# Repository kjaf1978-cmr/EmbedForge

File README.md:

# NETApps Electric Simulation

(Formerly EmbedForge; renamed by decision D18. The repository keeps its name.)

An offline-first desktop application that turns a plain-English description and a target
board into a verified, documented Arduino / Raspberry Pi / Pico project: firmware, pin map,
schematic, breadboard, PCB or perfboard, manufacturing files, BOM, emulation and assembly
guide.

Licence: GPL-3.0-or-later (LICENSE file added with the first code, Increment 1).

## Current state
**Version 0.2.0: Increment 2, schematic entry and circuit simulation** (decision D17, prompt
v3.9: design tools first).
- Schematic editor with a generic part library and live electrical rule check.
- Circuit simulator: operating point, transient, AC and DC sweep, cross-checked against
  ngspice; probes and a waveform viewer.
- Start screen with examples and a tutorial; projects with version history; SVG, PNG, SPICE
  and CSV export.

Next: Increment 3, PCB layout and routing. Increment 1 (shell, signed offline installers,
integrity check) is delivered as 0.1.0.

- Requirements baseline: `docs/requirements/EmbedForge_prompt_v3.9.md`
- Current increment: `docs/inc2/` (scope, test report, usability)
- Decisions: `docs/phase0/STATUS.md`; session log: `docs/SESSION_LOG.md`

## Layout
```
docs/requirements/   build prompt baselines, review findings, change logs
docs/phase0/         Phase 0 deliverables (a)–(o)
docs/inc1/           Increment 1 scope, reports, findings, user-executed procedures
docs/inc2/           Increment 2 scope, test report, usability
core/                Rust workspace: ef-schema, ef-cm, ef-integrity, ef-host, ef-diag,
                     ef-pack, ef-release, ef-install (embedforge-setup), ef-helper
packaging/           installation media: staging, signing scripts, .deb, specs, CI tests
app/ui/              UI (Preact + TypeScript + Vite), unit and browser tests
app/src-tauri/       Tauri 2 desktop shell
spikes/              Phase 0 evaluation code (not application code)
.github/workflows/   CI
tools/               scripts used to produce or check documents
```

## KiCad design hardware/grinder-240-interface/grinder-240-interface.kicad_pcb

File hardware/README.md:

# Boards of the worked designs (decisions D43, D44)

Each design's board as a KiCad 7 project, with its fabrication files. The boards are generated
from the app's schematics by `tools/kicad` and then checked with KiCad's design rule check
(DRC); do not edit the board files by hand without updating the plan in
`tools/kicad/layouts.ts`, or the next export overwrites the change.

| Design | Folder | Board | DRC (errors / unconnected) | Status |
|---|---|---|---|---|
| Mains voltage stabiliser 1 kVA (P4) | `stabiliser/` | 230 × 212 mm, 2 layers, 2 oz | 0 / 0 | routed; awaiting a person's review and a prototype |
| Mains change-over 1P, 32 A (P3): control board + DIN-rail panel | `changeover-1p/` | 155 × 110 mm, 2 layers, 2 oz | 0 / 0 | routed; panel wiring in `panel.csv` |
| Mains change-over 3P+N, 32 A (P3): control board + DIN-rail panel | `changeover-3p/` | 225 × 150 mm, 2 layers, 2 oz | 0 / 0 | routed; panel wiring in `panel.csv` |
| MPPT solar charger 48 V, 80 A (P6): power board | `mppt-power/` | 280 × 160 mm, 2 layers, 4 oz | 0 / 0 | routed; copper bars and lugs below |
| MPPT solar charger 48 V, 80 A (P6): control board | `mppt-control/` | 160 × 110 mm, 2 layers, 2 oz | 0 / 0 | routed; `link.csv`: the nets to the power board |
| Inverter 48 V 5 kW, 50 Hz transformer (P7a): power board | `inverter-lf-48-power/` | 280 × 170 mm, 2 layers, 4 oz | 0 / 0 | routed; copper bars and lugs, bus and ground planes |
| Inverter 48 V 5 kW, 50 Hz transformer (P7a): control board | `inverter-lf-48-control/` | 200 × 150 mm, 2 layers, 2 oz | 0 / 0 | routed; mains nets 3.2 mm apart |
| Inverter 48 V 5 kW, high-frequency (P7b): battery-side power board | `inverter-hf-48-power-lv/` | 180 × 230 mm, 2 layers, 4 oz | 0 / 0 | routed; copper bars, the current transformer off-board |
| Inverter 48 V 5 kW, high-frequency (P7b): 380 V power board | `inverter-hf-48-power-hv/` | 140 × 270 mm, 2 layers, 4 oz | 0 / 0 | routed; conformal coating required (0.8 mm, IPC-2221 B4); the drivers' HVG poured after routing |
| Inverter 48 V 5 kW, high-frequency (P7b): battery-side control board | `inverter-hf-48-control-lv/` | 220 × 160 mm, 2 layers, 2 oz | 0 / 0 | routed; `panel.csv`: the nets to the other boards (J_PANEL, J_PANEL2) |
| Inverter 48 V 5 kW, high-frequency (P7b): 380 V control board | `inverter-hf-48-control-hv/` | 340 × 240 mm, 2 layers, 2 oz | 0 / 0 | routed; 380 V nets 2.5 mm from the battery side; HVG poured on both layers; 77 links drawn by `tools/kicad/autolink.py`; `panel.csv`: the nets to the other boards |
| Inverter 12 V 1.5 kW, 50 Hz transformer (P7a): power board | `inverter-lf-12-power/` | 280 × 170 mm, 2 layers, 4 oz | 0 / 0 | routed; the 48 V board's plan with six 4700 µF bus capacitors |
| Inverter 12 V 1.5 kW, 50 Hz transformer (P7a): control board | `inverter-lf-12-control/` | 200 × 150 mm, 2 layers, 2 oz | 0 / 0 | routed; mains nets 3.2 mm apart; one link drawn by `tools/kicad/link.py` |
| Inverter 12 V 1.5 kW, high-frequency (P7b): battery-side power board | `inverter-hf-12-power-lv/` | 260 × 230 mm, 2 layers, 4 oz | 0 / 0 | routed; three MOSFETs per switch (twelve in the row), copper bars |
| Inverter 12 V 1.5 kW, high-frequency (P7b): 380 V power board | `inverter-hf-12-power-hv/` | 140 × 270 mm, 2 layers, 4 oz | 0 / 0 | routed; the 48 V board's plan; conformal coating required |
| Inverter 12 V 1.5 kW, high-frequency (P7b): battery-side control board | `inverter-hf-12-control-lv/` | 220 × 160 mm, 2 layers, 2 oz | 0 / 0 | routed; `panel.csv`: the nets to the other boards |
| Inverter 12 V 1.5 kW, high-frequency (P7b): 380 V control board | `inverter-hf-12-control-hv/` | 340 × 240 mm, 2 layers, 2 oz | 0 / 0 | routed; as the 48 V one (HVG pours, links by `autolink.py`) |
| Gate controller 24 V (P9, D25): motor drive, protections, Arduino Nano and IR receiver | `gate-controller/` | 160 × 110 mm, 2 layers, 2 oz | 0 / 0 | routed; the Nano on sockets, the TSOP38238 behind the enclosure's window; one supply link drawn by `tools/kicad/link.py` |
| Pump controller (P9): control board + DIN-rail panel | `pump-control/` | 165 × 110 mm, 2 layers, 2 oz | 0 / 0 | routed; mains nets 3.2 mm apart; panel wiring in `panel.csv` |
| Cordless trimmer drive 36 V (P9) | `trimmer-drive/` | 160 × 100 mm, 2 layers, 4 oz | 0 / 0 | routed; power on 3 mm tracks, ground poured on both layers |
| Block moulding machine (P9): safety circuit, 24 V outputs, inputs and Arduino Nano + DIN-rail panel | `block-machine/` | 170 × 120 mm, 2 layers, 2 oz | 0 / 0 | routed; the pump, mixer and vibrator contactors, E-stop and safety contactors on the DIN rail, wiring in `panel.csv`; no 400 V net on the board |
| Irrigation controller (P9, D24): main board | `irrigation-main/` | 130 × 100 mm, 2 layers, 2 oz | 0 / 0 | routed; ESP32-DevKitC on sockets (antenna over the top edge), 24 V in, bus to the modules (20-way ribbon) |
| Irrigation controller (P9, D24): 8-zone channel module (1 … 8 per controller) | `irrigation-module/` | 230 × 95 mm, 2 layers, 2 oz | 0 / 0 | routed; field terminals along the bottom edge (per zone: valve +24 V, valve out, sensor +3.3 V, signal, 0 V); bus in top left, out top right |
| Grinder drive 2.5 kW, 240 V (P9, D26/D46): power board | `grinder-240-power/` | 160 × 110 mm, 2 layers, 4 oz | 0 / 0 | routed; GBPC3510 bridge and both IKW50N60T on the bottom edge (one heatsink, insulating pads), 3 mm power tracks, ground poured on both layers; the whole board at mains potential: 0.8 mm between nets (1.5 mm around the mains input), conformal coating required; the 15 mH choke, the motor and the contactor KM on the panel (`panel.csv`) |
| Grinder drive 2.5 kW, 240 V (P9, D26/D46): control board | `grinder-240-control/` | 180 × 130 mm, 2 layers, 2 oz | 0 / 0 | routed (the run chain and the speed pot moved to the operator interface board); the five trimmers (MAX, MIN, ACCEL, CURRENT LIMIT, IR COMP), terminals for E-STOP, STOP, START, the thermal switch, the reversing switch's contact and the speed pot; not isolated from the mains (DFMEA GR-9): inside the closed enclosure only; one link drawn by `tools/kicad/link.py` |
| Grinder drive 2.5 kW, 240 V (P9, D26/D46): operator interface board | `grinder-240-interface/` | 120 × 90 mm, 2 layers, 2 oz | 0 / 0 | routed; the PELV side (run chain, E-STOP, STOP, START, thermal and reversing contacts, QEN for the K1 and KM coils, the speed pot with MAX and MIN, its TL431 reference) and the barrier: the AMC1311B (set point) and the PC817 (fault); 5.5 mm between the PELV nets and the control's side (GND, V12, VD2, SPP, SPN, OKA: J_MAINS, its spare pole on V12); TR1 on the panel |
| Grinder drive 2.5 kW, 24 V battery (P9, D26/D46): power board | `grinder-24-power/` | 200 × 130 mm, 2 layers, 4 oz | 0 / 0 | routed; six IRFP4468 on the bottom edge, the switch node a 6 mm bar between the row and the edge (tin it), bus plane over 8 × 2200 µF, ground plane, the motor's return poured to the 0.5 mΩ shunt; M5 lugs for battery +/−, motor A+/A−; the 200 A fuse, KM (250 A) and K1 on the panel |
| Grinder drive 2.5 kW, 24 V battery (P9, D26/D46): control board | `grinder-24-control/` | 180 × 130 mm, 2 layers, 2 oz | 0 / 0 | routed; the 240 V control's circuit with the 24 V scaling and the battery's 21 V cut-off |
| Mains stabiliser 5/10/15 kVA, thyristor taps (P4b, D41): logic board | `stabiliser-t-logic/` | 205 × 140 mm, 2 layers, 2 oz | 0 / 0 | routed; mains nets 3.2 mm apart; thyristors, autotransformer and the pair boards wired per `panel.csv` |
| Mains stabiliser 5/10/15 kVA, thyristor taps (P4b): thyristor pair driver (7 per unit) | `stabiliser-t-pair/` | 120 × 80 mm, 2 layers, 2 oz | 0 / 0 | routed; optotriac isolation to the logic side (DIP-6 with pin 5 removed); `panel.csv`: J_MAINS/J_PANEL wiring |

### The 24 V inverters (P7, 3 kW)

The 24 V units use the 48 V boards: the same parts on each board with the same footprints and
connections, only values differ (`tools/kicad/variant.ts` checks this). The 48 V board's folder
holds the 24 V parts list as `<board>-bom-24v.csv`; order the board's fabrication files as they
are and fit the parts from that list.

## What a folder holds

- `<design>.kicad_pcb`, `.kicad_pro`, `.kicad_dru`: the board, its net classes and the custom
  insulation rule. Open the `.kicad_pro` in KiCad 7 or later.
- `<design>-fabrication.zip`: Gerber (copper, solder mask, silkscreen, outline), Excellon drill
  file and drill map, pick-and-place positions. Upload it to the fab as it is.
- `<design>-copper.pdf` / `.png`: both copper layers, the silkscreen and the outline.
- `<design>-drc.rpt`: KiCad's DRC report of the routed board.
- `panel.csv`: for designs with parts on a panel (DIN rail, chassis), the wiring list.
- `fp-lib-table` with `../NETApps.pretty`: the app's footprints as a KiCad library.

## Rules every board follows

- Mains nets (found from the schematic: everything galvanically joined to L and N, up to the
  transformers, optocouplers and relay coils) are 3.2 mm from every other net, the creepage of
  basic insulation at 300 V r.m.s. (IEC 62368-1, pollution degree 2, material group IIIb); the
  control side is earthed (PE), so basic insulation suffices. Between two mains nets 1.5 mm.
- Mains terminals at 7.62 mm pitch; off-board transformers on connectors with an empty pole
  between their windings.
- Footprints follow each part's value and rating, as the parts list orders it: electrolytics by
  C·V (Ø 5 … 18 mm radial, 22 … 35 mm snap-in), film capacitors by C·V (7.5 … 37.5 mm pitch),
  Y and high-voltage ceramics at 10 mm, resistors by power (¼ W, 1 W, 2–3 W, 5 W and 10 W
  cement, four-terminal shunts), fuses (TR5 to 6.3 A, 5 × 20 mm holder to 10 A), inductors (radial
  to 2 A, toroid to 10 A). Parts above that (power resistors over 10 W, inductors over 10 A, fuses
  over 10 A) sit off the board, on the chassis or heatsink, wired or bolted.
- High-current nets end on M5 bolt lugs (busbars or cable lugs), not on screw terminals.
- Track widths by IPC-2221 for the current at 20 K rise in 2 oz copper (the stabiliser's mains
  tracks 1.6 mm for 7 A).
- The power section is placed and partly routed by a written plan (`tools/kicad/layouts.ts`);
  the control section is placed from the schematic and routed by Freerouting.

## Power boards (D45)

The high-current paths are drawn as 4 mm tracks with the solder mask open on them: solder a
tinned copper bar 4 × 3 mm (12 mm², 80 A at about 30 K rise) along each, or two 4 mm² solid
copper wires, so the bar carries the current and the board's 4 oz copper only joins it to the
pins. Cables and busbars bolt to the M5 lugs (plated holes with 12 mm rings): the inductor and
the fuse sit on the chassis next to the board. The TO-247 and TO-126 parts stand in one row along
the bottom edge, their tabs to a common heatsink (isolate each tab with a thermal pad rated for
the voltage, the PV side reaches 114 V). The two boards of a design connect through their 12-pole
connectors, pole by pole as `link.csv` lists them.

## Parts lists

Each folder's `<design>-bom.csv` lists the parts with the footprint each has on the board, the
manufacturer's part number, distributors with order numbers, and an indicative unit price (EUR,
October 2026, "live" or "estimate"; check prices and stock when ordering). The lines not on
this board come last (panel parts, the other board's parts).

## Known warnings

- `lib_footprint_mismatch` on parts turned 180°: KiCad compares the turned reference text's angle
  with the library copy; the copper is the same.
- `silk_overlap`: reference designators touching outlines (cosmetic; fix by hand before ordering
  if the silkscreen matters).

## Before ordering

These boards come out of the verified schematics, but no one has built them yet. Before a
production order: a person's review of the layout (clearances on the mains side, the heat of the
relays and regulators), and a prototype tested against the design's test plan (TEST_REPORT.md).
Prices and parts: the design document's BOM (`docs` export in the app).

Regenerate a board:

```
cd app/ui && npx vite-node ../../tools/kicad/export.ts stabiliser /tmp/stab
cd ../.. && python3 tools/kicad/route.py /tmp/stab --passes 40
```

Needs KiCad 7 (pcbnew Python module and kicad-cli), Freerouting 1.9 at
/opt/freerouting/freerouting.jar (or `FREEROUTING=`), Java 17+ and xvfb-run.

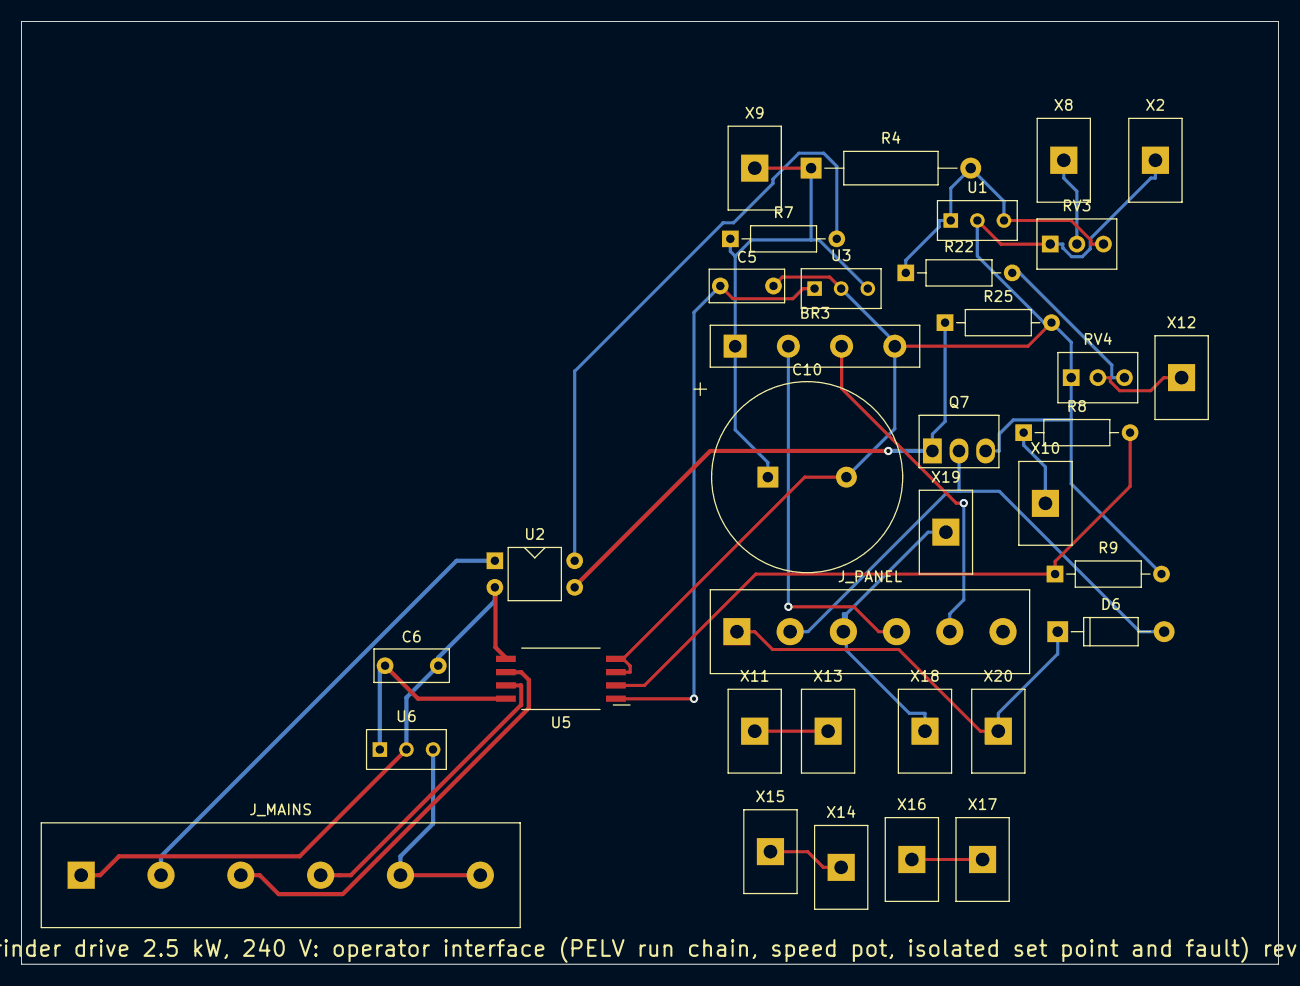
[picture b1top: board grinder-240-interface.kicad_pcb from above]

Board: 2 copper layers, 120.0 x 90.0 mm, 35 parts (0 on the bottom side), 25 nets.

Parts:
BR3: KBP206; Bridge_Inline_4
C5, C6: 100n; C_Disc_5.08
C10: 1000u; CP_Radial_D18
D6: 1N4007; D_DO-41
J_MAINS: mains to the panel; TerminalBlock_1x6_P7.62
J_PANEL: to the panel; TerminalBlock_1x6
Q7: IRLZ44N; TO-220_Vertical
R4: 1.5k; R_Axial_0309
R7, R25: 10k; R_Axial_0207
R8, R9: 100k; R_Axial_0207
R22: 3.9k; R_Axial_0207
RV3, RV4: 1k; Pot_Trimmer_3
U1: TL431; TO-92_Wide
U2: PC817; DIP-4
U3, U6: L78L05; TO-92_Wide
U5: AMC1311B; SOIC-8W
X2: PE: the PELV 0 V bonded to protective earth; TerminalBlock_1x1
X8: speed pot top; TerminalBlock_1x1
X9: E-STOP (NC) from +24 V; TerminalBlock_1x1
X10: speed pot wiper; TerminalBlock_1x1
X11: E-STOP (NC) return; TerminalBlock_1x1
X12: speed pot bottom; TerminalBlock_1x1
X13: STOP (NC); TerminalBlock_1x1
X14: STOP (NC) return; TerminalBlock_1x1
X15: motor thermal switch (NC); TerminalBlock_1x1
X16: motor thermal switch return; TerminalBlock_1x1
X17: reversing switch auxiliary (closed in FWD and REV); TerminalBlock_1x1
X18: reversing switch auxiliary return; TerminalBlock_1x1
X19: START (NO); TerminalBlock_1x1
X20: START (NO) return; TerminalBlock_1x1

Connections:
CH2: D6.1, J_PANEL.1, X20.1
CR: D6.2, J_PANEL.2, Q7.2
ESO: X11.1, X13.1
GND: C6.2, J_MAINS.1, U2.2, U5.5, U6.2
OKA: J_MAINS.2, U2.1
OKC: R7.2, U2.4
OKG: Q7.1, R25.1, U2.3
PE0: BR3.4, C5.2, C10.2, Q7.3, R9.2, R25.2, RV3.1, RV4.1, U1.2, U3.2, U5.3, U5.4, X2.1
RV: J_PANEL.3, X18.1, X19.1
SMN: RV4.2, X12.1
SMX: RV3.2, X8.1
SPN: J_MAINS.3, U5.6
SPP: J_MAINS.4, U5.7
SREF: R4.2, R22.1, RV3.3, U1.1, U1.3
STO: X14.1, X15.1
TA: BR3.2, J_PANEL.4
TB: BR3.3, J_PANEL.5
THO: X16.1, X17.1
V12: J_MAINS.5, J_MAINS.6, U6.3
V24: BR3.1, C10.1, R4.1, R7.1, U3.3, X9.1
VD1: C5.1, U3.1, U5.1
VD2: C6.1, U5.8, U6.1
VMN: R22.2, RV4.3
WIP: R8.1, X10.1
WIPD: R8.2, R9.1, U5.2

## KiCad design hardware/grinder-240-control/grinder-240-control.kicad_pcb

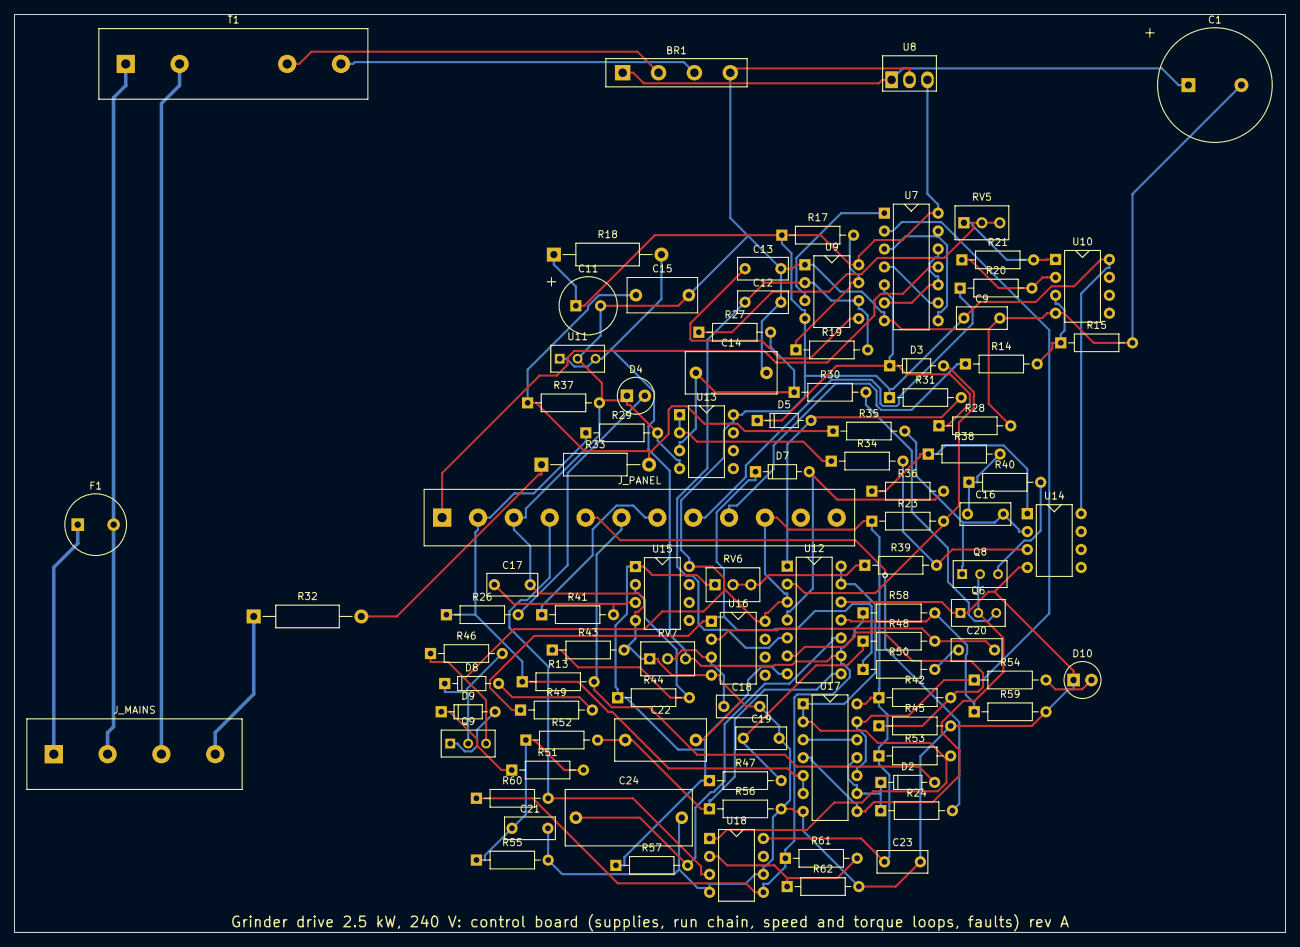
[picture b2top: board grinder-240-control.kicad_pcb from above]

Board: 2 copper layers, 180.0 x 130.0 mm, 94 parts (0 on the bottom side), 69 nets.

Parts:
BR1: KBP206; Bridge_Inline_4
C1: 470u; CP_Radial_D16
C9, C18, C20, C21, C23: 100n; C_Disc_5.08
C11: 47u; CP_Radial_D8
C12, C13: 10n; C_Disc_5.08
C14: 4.7u; C_Film_P10
C15: 2.2u; C_Film_P7.5
C16: 47n; C_Disc_5.08
C17: 1n; C_Disc_5.08
C19: 1u; C_Disc_5.08
C22: 10u; C_Film_P10
C24: 22u; C_Film_P15
D2, D3, D5, D7, D9: 1N4148; D_DO-35
D4: green; LED_D5.0
D8: BZX55C5V1; D_DO-35
D10: red; LED_D5.0
F1: 0.2; F_TR5
J_MAINS: mains to the panel; TerminalBlock_1x4_P7.62
J_PANEL: to the panel; TerminalBlock_1x12
Q6, Q8: 2N7000; TO-92_Wide
Q9: BC557B; TO-92_Wide
R13, R14, R20, R23, R29, R31, R34, R37, R45, R47, R48, R49, R53, R59, R60: 10k; R_Axial_0207
R15, R21: 20k; R_Axial_0207
R17: 6.8k; R_Axial_0207
R18: 470; R_Axial_0309
R19: 330; R_Axial_0207
R24: 4.7k; R_Axial_0207
R26, R36, R54: 2.2k; R_Axial_0207
R27: 22k; R_Axial_0207
R28, R35, R39: 100k; R_Axial_0207
R30, R40: 100; R_Axial_0207
R32, R33: 453k; R_Axial_0309
R38, R55, R56, R57: 1M; R_Axial_0207
R41, R43, R51, R62: 1k; R_Axial_0207
R42: 30.1k; R_Axial_0207
R44: 9.09k; R_Axial_0207
R46, R50: 47k; R_Axial_0207
R52: 330k; R_Axial_0207
R58: 4.42k; R_Axial_0207
R61: 9.31k; R_Axial_0207
RV5, RV6: 1M; Pot_Trimmer_3
RV7: 1k; Pot_Trimmer_3
T1: 0.0625; Transformer_Wires_P7.62
U7, U17: V12; DIP-14
U8: 7812; TO-220_Vertical
U9: NE555; DIP-8
U10, U13, U14, U15, U16: LM358; DIP-8
U11: TL431; TO-92_Wide
U12: LM339; DIP-14
U18: LM393; DIP-8

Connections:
ACW: R27.1, RV5.2, RV5.3
CLE: D9.2, Q9.1
CLF: C21.1, R51.2, R52.1, R55.1
CLJ: D9.1, R51.1
CLK: U7.1, U9.3
CT: C12.1, R19.2, U9.2, U9.6, U12.5
CV: C13.1, U9.5
DIS: R17.2, R19.1, U9.7
DRV: J_PANEL.1, U7.11
DUT: D7.2, R36.2, U12.4
DUTP: R36.1, R38.1, U14.1
EN: J_PANEL.2, R13.1, R26.1, R29.1, U17.5, U17.6
ENL: D4.2, R26.2
ENN: Q6.2, Q8.2, U17.4, U17.8
FBA: R32.2, R33.1
FBD: C15.1, R33.2, R35.1, R37.1
FLT: R54.1, U7.2, U17.10, U17.13
FLTH: U17.3, U17.12
FLTN: R53.2, U12.13, U12.14, U17.1, U17.2, U18.1
GND: BR1.4, C1.2, C9.2, C11.2, C12.2, C13.2, C14.2, C15.2, C17.2, C18.2, C19.2, C21.2, C22.2, C23.2, C24.2, D4.1, D10.1, J_PANEL.3, Q6.1, R15.2, R28.2, R29.2, R37.2, R43.2, R45.2, R55.2, R56.2, R59.2, R62.2, RV7.1, U7.7, U8.2, U9.1, U10.4, U11.2, U12.12, U13.4, U14.4, U15.4, U16.4, U17.7, U18.4, U18.6
IAF: C19.1, R47.2, R48.1
IAV: C22.1, R52.2, R56.1, U12.8
IOL: C24.1, R57.2, U12.10
IRW: R39.1, RV6.2, RV6.3
ISA: R44.1, R47.1, R57.1, RV6.1, U12.7, U15.1
ISN: R43.1, R44.2, U15.2
ISP: C17.1, R41.2, U15.3
JB: D8.1, Q9.2, R46.2
JD1: D8.2, R49.2
L: F1.1, J_MAINS.1
LFA: D10.2, R54.2
LT: F1.2, J_MAINS.2, T1.1
N: J_MAINS.3, T1.2
NTH: J_PANEL.4, R60.2, U18.3
OK: D2.1, R24.1, U17.9, U17.11
OKA: J_PANEL.5, R24.2
PIN: C16.2, Q8.1, R35.2, U14.2
PIQ: Q8.3, R40.2
PIX: C16.1, R38.2, R40.1
Q: U7.4, U7.9
QN: U7.6, U7.10, U7.12
RCLO: D5.2, R31.2, U12.1
RPW: D3.2, R23.2, U12.2
RST: D3.1, D5.1, R28.1, U7.5
SDM: R20.2, R21.1, U10.2
SDN: D2.2, J_PANEL.6, R13.2
SDP: R14.2, R15.1, U10.3
SET: U7.3, U7.8, U7.13
SHN: J_PANEL.7, R41.1
SPB: R34.1, U13.1, U13.2
SPC: R34.2, R39.2, U14.3
SPN: J_PANEL.8, R20.1
SPP: J_PANEL.9, R14.1
SPQ: Q6.3, R30.2
SPR: C14.1, R27.2, R30.1, U13.3
SWN: J_MAINS.4, R32.1
TC: BR1.2, T1.3
TD: BR1.3, T1.4
TLN: C20.2, R48.2, U16.2
TLO: D7.1, R49.1, R50.1, U16.1
TLX: C20.1, R50.2
V12: C9.1, C11.1, C23.1, J_PANEL.10, Q9.3, R17.1, R18.1, R23.1, R31.1, R42.1, R46.1, R53.1, U7.14, U8.3, U9.4, U9.8, U10.8, U12.3, U13.8, U14.8, U15.8, U16.8, U17.14, U18.8
V15: BR1.1, C1.1, U8.1
VCL: C18.1, RV7.2, U16.3
VOL: R58.2, R59.1, U12.11
VOT: R61.2, R62.1, U18.2
VPK: R42.2, R45.1, U12.6
VREF: R18.2, R58.1, R60.1, R61.1, RV7.3, U11.1, U11.3, U12.9, U18.5
WIPM: R21.2, RV5.1, U10.1

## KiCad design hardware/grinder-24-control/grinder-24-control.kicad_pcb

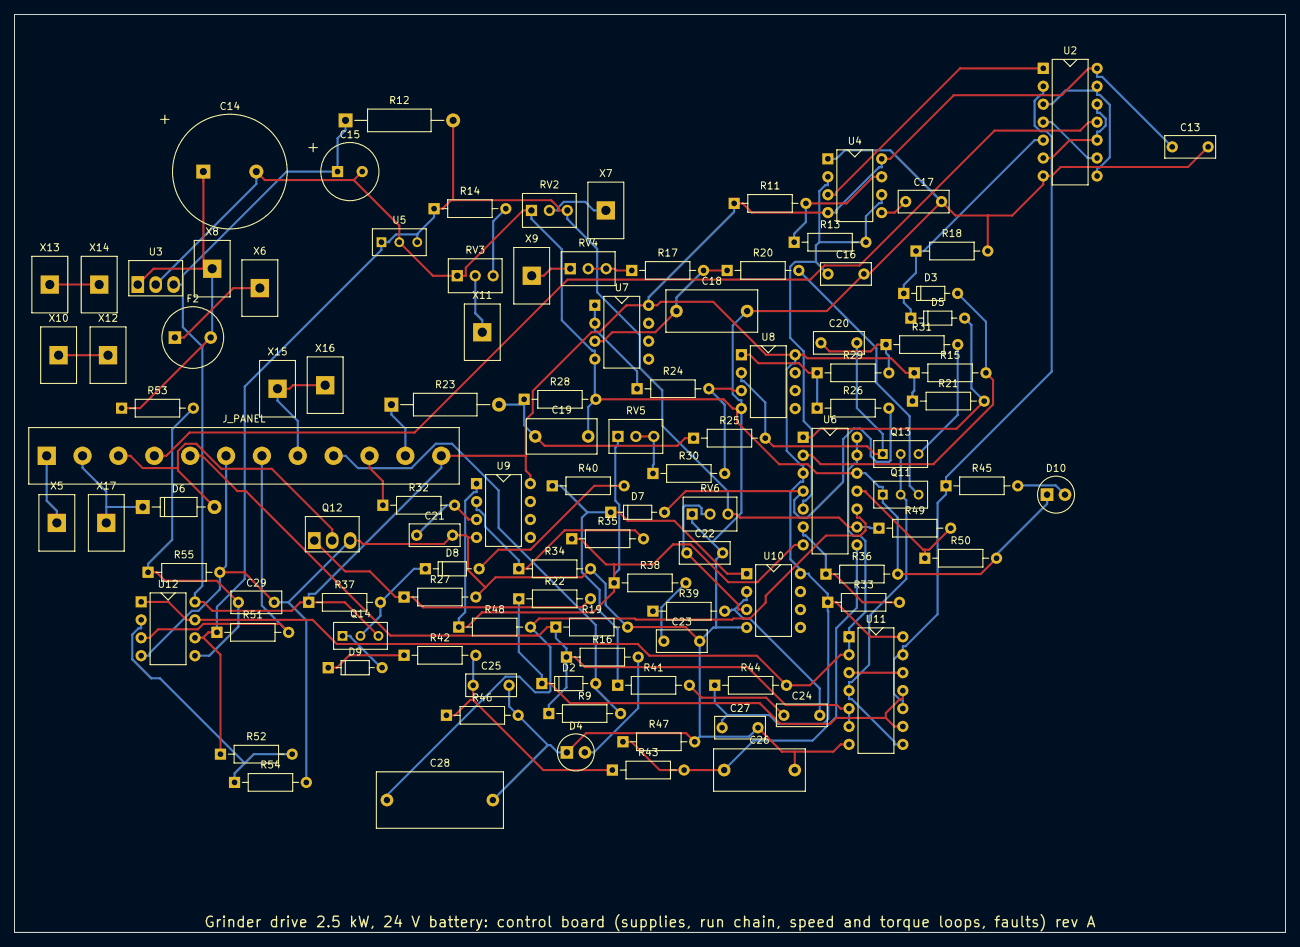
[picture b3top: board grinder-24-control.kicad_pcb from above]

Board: 2 copper layers, 180.0 x 130.0 mm, 107 parts (0 on the bottom side), 70 nets.

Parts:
C13, C22, C23, C24, C25, C27, C29: 100n; C_Disc_5.08
C14: 220u; CP_Radial_D16
C15: 47u; CP_Radial_D8
C16, C17: 10n; C_Disc_5.08
C18: 4.7u; C_Film_P10
C19: 2.2u; C_Film_P7.5
C20: 47n; C_Disc_5.08
C21: 1n; C_Disc_5.08
C26: 10u; C_Film_P10
C28: 22u; C_Film_P15
D2, D3, D5, D7, D9: 1N4148; D_DO-35
D4: green; LED_D5.0
D6: 1N4007; D_DO-41
D8: BZX55C5V1; D_DO-35
D10: red; LED_D5.0
F2: 3.15; F_TR5
J_PANEL: to the panel; TerminalBlock_1x12
Q11, Q13: 2N7000; TO-92_Wide
Q12: IRLZ44N; TO-220_Vertical
Q14: BC557B; TO-92_Wide
R9, R15, R19, R21, R24, R28, R36, R38, R39, R40, R44, R50, R51, R55: 10k; R_Axial_0207
R11: 6.8k; R_Axial_0207
R12: 470; R_Axial_0309
R13: 330; R_Axial_0207
R14: 3.9k; R_Axial_0207
R16, R26, R45: 2.2k; R_Axial_0207
R17: 22k; R_Axial_0207
R18, R25, R27, R30: 100k; R_Axial_0207
R20, R31: 100; R_Axial_0207
R22, R32, R34, R42, R54: 1k; R_Axial_0207
R23: 110k; R_Axial_0309
R29, R46, R47, R48: 1M; R_Axial_0207
R33: 30.1k; R_Axial_0207
R35: 24.3k; R_Axial_0207
R37, R41: 47k; R_Axial_0207
R43: 330k; R_Axial_0207
R49: 4.42k; R_Axial_0207
R52: 9.31k; R_Axial_0207
R53: 73.2k; R_Axial_0207
RV2, RV3, RV6: 1k; Pot_Trimmer_3
RV4, RV5: 1M; Pot_Trimmer_3
U2, U11: V12; DIP-14
U3: 7812; TO-220_Vertical
U4: NE555; DIP-8
U5: TL431; TO-92_Wide
U6: LM339; DIP-14
U7, U8, U9, U10: LM358; DIP-8
U12: LM393; DIP-8
X5: key switch (from battery +); TerminalBlock_1x1
X6: key switch (to the drive); TerminalBlock_1x1
X7: speed pot top; TerminalBlock_1x1
X8: E-STOP (NC) from +24 V; TerminalBlock_1x1
X9: speed pot wiper; TerminalBlock_1x1
X10: E-STOP (NC) return; TerminalBlock_1x1
X11: speed pot bottom; TerminalBlock_1x1
X12: STOP (NC); TerminalBlock_1x1
X13: STOP (NC) return; TerminalBlock_1x1
X14: motor thermal switch (NC); TerminalBlock_1x1
X15: motor thermal switch return; TerminalBlock_1x1
X16: START (NO); TerminalBlock_1x1
X17: START (NO) return; TerminalBlock_1x1

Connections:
ACW: R17.1, RV4.2, RV4.3
BAT: J_PANEL.1, X5.1
CH2: D6.1, J_PANEL.2, X17.1
CLE: D9.2, Q14.1
CLF: C25.1, R42.2, R43.1, R46.1
CLJ: D9.1, R42.1
CLK: U2.1, U4.3
CR: D6.2, J_PANEL.3, Q12.2
CT: C16.1, R13.2, U4.2, U4.6, U6.5
CV: C17.1, U4.5
DIS: R11.2, R13.1, U4.7
DRV: J_PANEL.4, U2.11
DUT: D7.2, R26.2, U6.4
DUTP: R26.1, R29.1, U8.1
EN: J_PANEL.5, R9.1, R16.1, R19.1, U11.5, U11.6
ENL: D4.2, R16.2
ENN: Q11.2, Q13.2, U11.4, U11.8
ESO: X10.1, X12.1
FBD: C19.1, R23.2, R25.1, R28.1
FLT: R45.1, U2.2, U11.10, U11.13
FLTH: U11.3, U11.12
FLTN: R44.2, U6.13, U6.14, U11.1, U11.2, U12.1, U12.7
GND: C13.2, C14.2, C15.2, C16.2, C17.2, C18.2, C19.2, C21.2, C22.2, C23.2, C25.2, C26.2, C27.2, C28.2, C29.2, D4.1, D10.1, J_PANEL.6, Q11.1, Q12.3, R18.2, R19.2, R27.2, R28.2, R34.2, R36.2, R46.2, R47.2, R50.2, R54.2, R55.2, RV2.1, RV3.1, RV6.1, U2.7, U3.2, U4.1, U5.2, U6.12, U7.4, U8.4, U9.4, U10.4, U11.7, U12.4
IAF: C23.1, R38.2, R39.1
IAV: C26.1, R43.2, R47.1, U6.8
IOL: C28.1, R48.2, U6.10
IRW: R30.1, RV5.2, RV5.3
ISA: R35.1, R38.1, R48.1, RV5.1, U6.7, U9.1
ISN: R34.1, R35.2, U9.2
ISP: C21.1, R32.2, U9.3
JB: D8.1, Q14.2, R37.2
JD1: D8.2, R40.2
LFA: D10.2, R45.2
NTH: J_PANEL.7, R51.2, U12.3
OK: D2.1, R22.1, U11.9, U11.11
OKG: Q12.1, R22.2, R27.1
PIN: C20.2, Q13.1, R25.2, U8.2
PIQ: Q13.3, R31.2
PIX: C20.1, R29.2, R31.1
Q: U2.4, U2.9
QN: U2.6, U2.10, U2.12
RCLO: D5.2, R21.2, U6.1
RPW: D3.2, R15.2, U6.2
RST: D3.1, D5.1, R18.1, U2.5
RV: J_PANEL.8, X15.1, X16.1
SDN: D2.2, J_PANEL.9, R9.2
SET: U2.3, U2.8, U2.13
SHN: J_PANEL.10, R32.1
SMN: RV3.2, X11.1
SMX: RV2.2, X7.1
SPB: R24.1, U7.1, U7.2
SPC: R24.2, R30.2, U8.3
SPQ: Q11.3, R20.2
SPR: C18.1, R17.2, R20.1, U7.3
STO: X13.1, X14.1
SWN: J_PANEL.11, R23.1
TLN: C24.2, R39.2, U10.2
TLO: D7.1, R40.1, R41.1, U10.1
TLX: C24.1, R41.2
V12: C13.1, C15.1, C27.1, J_PANEL.12, Q14.3, R11.1, R12.1, R15.1, R21.1, R33.1, R37.1, R44.1, U2.14, U3.3, U4.4, U4.8, U6.3, U7.8, U8.8, U9.8, U10.8, U11.14, U12.8
V24: C14.1, F2.2, R53.1, U3.1, X8.1
VBD: C29.1, R53.2, R55.1, U12.5
VCL: C22.1, RV6.2, U10.3
VK: F2.1, X6.1
VMN: R14.2, RV3.3
VOL: R49.2, R50.1, U6.11
VOT: R52.2, R54.1, U12.2
VPK: R33.2, R36.1, U6.6
VREF: R12.2, R14.1, R49.1, R51.1, R52.1, RV2.3, RV6.3, U5.1, U5.3, U6.9, U12.6
WIP: RV4.1, X9.1

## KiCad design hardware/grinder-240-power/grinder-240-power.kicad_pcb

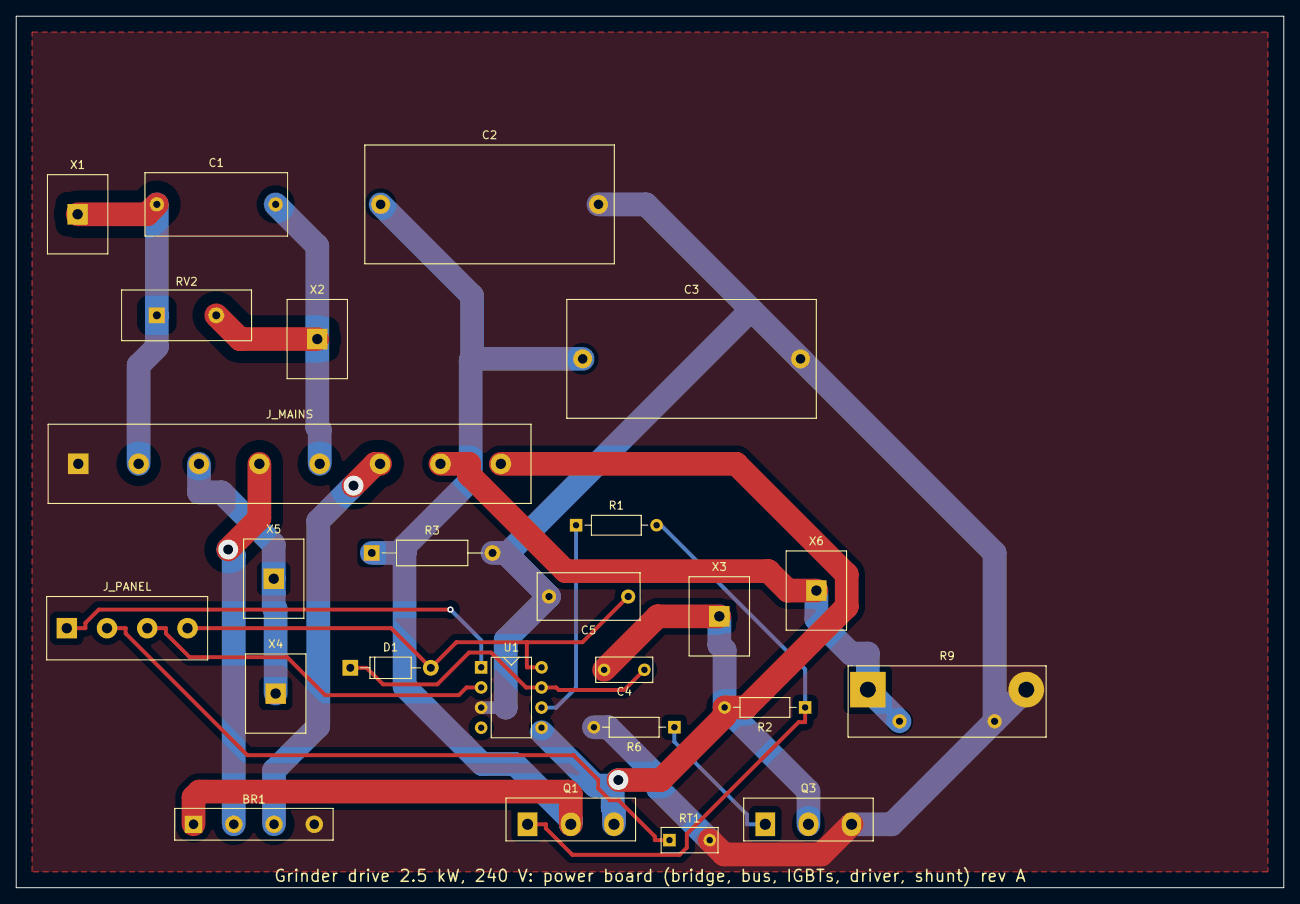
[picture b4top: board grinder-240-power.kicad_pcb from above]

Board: 2 copper layers, 160.0 x 110.0 mm, 25 parts (0 on the bottom side), 17 nets.

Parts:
BR1: GBPC3510; Bridge_Inline_4
C1: 1u; C_Film_P15
C2, C3: 10u; C_Film_P27.5
C4: 1u; C_Disc_5.08
C5: 10u; C_Film_P10
D1: UF4007; D_DO-41
J_MAINS: mains to the panel; TerminalBlock_1x8_P7.62
J_PANEL: to the panel; TerminalBlock_1x4
Q1, Q3: IKW50N60T; TO-247_Vertical
R1: 10; R_Axial_0207
R2: 10k; R_Axial_0207
R3: 220k; R_Axial_0309
R6: 1; R_Axial_0207
R9: 0.01; R_Shunt_4T
RT1: 10k; RT_Disc_5.08
RV2: 14D471K; MOV_Disc_14
U1: IR2184-type 600 V; DIP-8
X1: L (from the C16 breaker); TerminalBlock_1x1_P7.62
X2: N; TerminalBlock_1x1_P7.62
X3: armature choke (from the switch node); TerminalBlock_1x1_P7.62
X4: armature choke (to the motor); TerminalBlock_1x1_P7.62
X5: motor A+ (through the reversing switch); TerminalBlock_1x1_P7.62
X6: motor A- (through the reversing switch); TerminalBlock_1x1_P7.62

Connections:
BUS: BR1.1, C2.1, C3.1, Q1.2, R3.1
DRV: J_PANEL.1, U1.1
GH: Q1.1, R1.2, R2.1
GL: Q3.1, R6.1
GND: BR1.4, C2.2, C3.2, C5.2, J_MAINS.1, Q3.3, R3.2, R6.2, R9.2, R9.4, RT1.2, U1.3
HO: R1.1, U1.6
L: C1.1, J_MAINS.2, RV2.1, X1.1
LAO: J_MAINS.3, X4.1, X5.1
LK: BR1.2, J_MAINS.4
N: C1.2, J_MAINS.5, RV2.2, X2.1
NK: BR1.3, J_MAINS.6
NTH: J_PANEL.2, RT1.1
SDN: J_PANEL.3, U1.2
SHN: J_MAINS.7, R9.1, R9.3, X6.1
SWN: C4.2, J_MAINS.8, Q1.3, Q3.2, R2.2, U1.5, X3.1
V12: C5.1, D1.2, J_PANEL.4, U1.8
VBS: C4.1, D1.1, U1.7

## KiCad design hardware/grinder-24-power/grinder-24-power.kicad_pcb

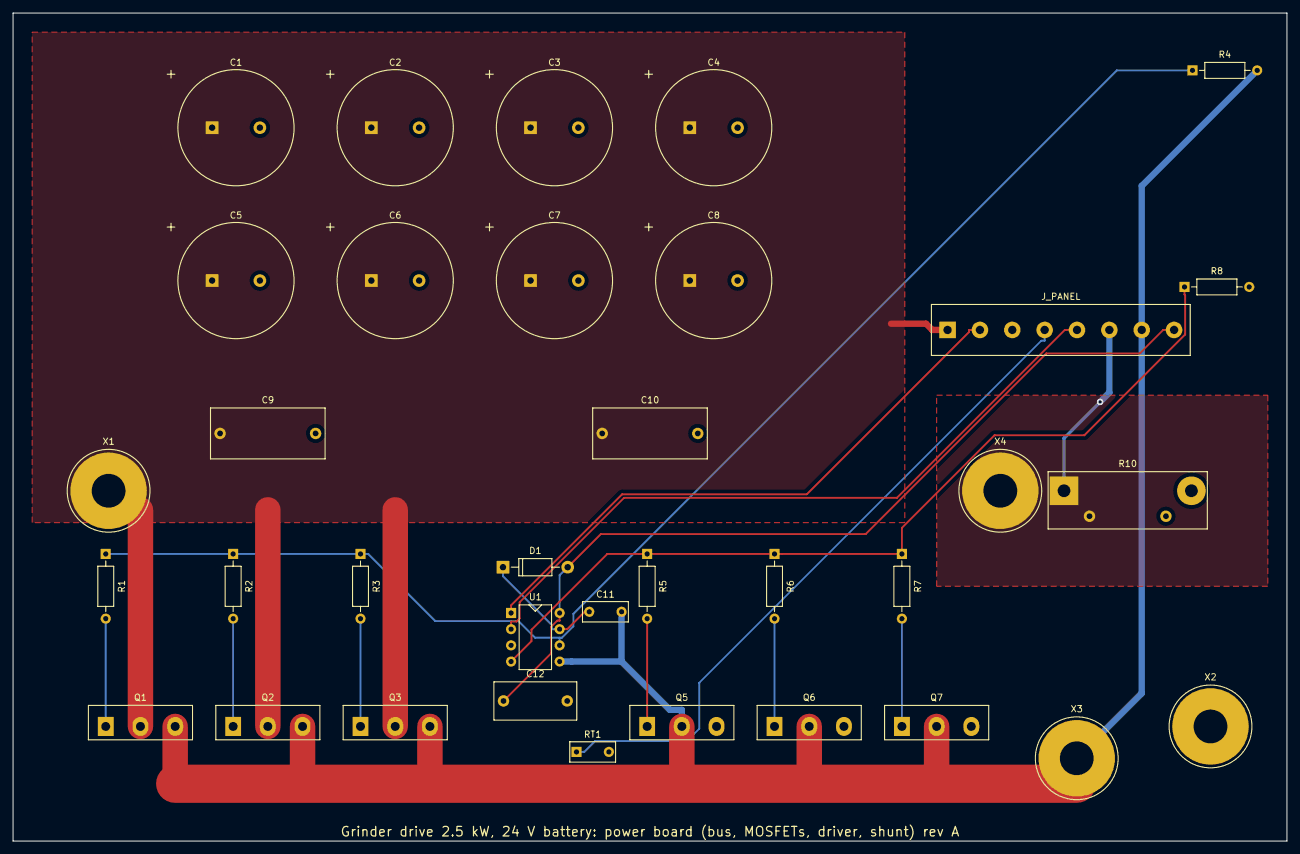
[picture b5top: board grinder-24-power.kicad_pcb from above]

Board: 2 copper layers, 200.0 x 130.0 mm, 35 parts (0 on the bottom side), 17 nets.

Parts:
C1, C2, C3, C4, C5, C6, C7, C8: 2200u; CP_Radial_D18
C9, C10: 10u; C_Film_P15
C11: 1u; C_Disc_5.08
C12: 10u; C_Film_P10
D1: UF4007; D_DO-41
J_PANEL: to the panel; TerminalBlock_1x8
Q1, Q2, Q3, Q5, Q6, Q7: IRFP4468; TO-247_Vertical
R1, R2, R3, R5, R6, R7: 4.7; R_Axial_0207
R4, R8: 10k; R_Axial_0207
R10: 0.0005; R_Shunt_4T
RT1: 10k; RT_Disc_5.08
U1: IR2184-type 600 V; DIP-8
X1: battery + (through the 200 A fuse and KM); Lug_M5
X2: battery -; Lug_M5
X3: motor A+; Lug_M5
X4: motor A-; Lug_M5

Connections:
BUS: C1.1, C2.1, C3.1, C4.1, C5.1, C6.1, C7.1, C8.1, C9.1, C10.1, J_PANEL.1, Q1.2, Q2.2, Q3.2, X1.1
DRV: J_PANEL.2, U1.1
GH1: Q1.1, R1.2
GH2: Q2.1, R2.2
GH3: Q3.1, R3.2
GL1: Q5.1, R5.2
GL2: Q6.1, R6.2
GL3: Q7.1, R7.2
GND: C1.2, C2.2, C3.2, C4.2, C5.2, C6.2, C7.2, C8.2, C9.2, C10.2, C12.2, J_PANEL.3, Q5.3, Q6.3, Q7.3, R8.2, R10.2, R10.4, RT1.2, U1.3, X2.1
HO: R1.1, R2.1, R3.1, R4.1, U1.6
LO: R5.1, R6.1, R7.1, R8.1, U1.4
NTH: J_PANEL.4, RT1.1
SDN: J_PANEL.5, U1.2
SHN: J_PANEL.6, R10.1, R10.3, X4.1
SWN: C11.2, J_PANEL.7, Q1.3, Q2.3, Q3.3, Q5.2, Q6.2, Q7.2, R4.2, U1.5, X3.1
V12: C12.1, D1.2, J_PANEL.8, U1.8
VBS: C11.1, D1.1, U1.7

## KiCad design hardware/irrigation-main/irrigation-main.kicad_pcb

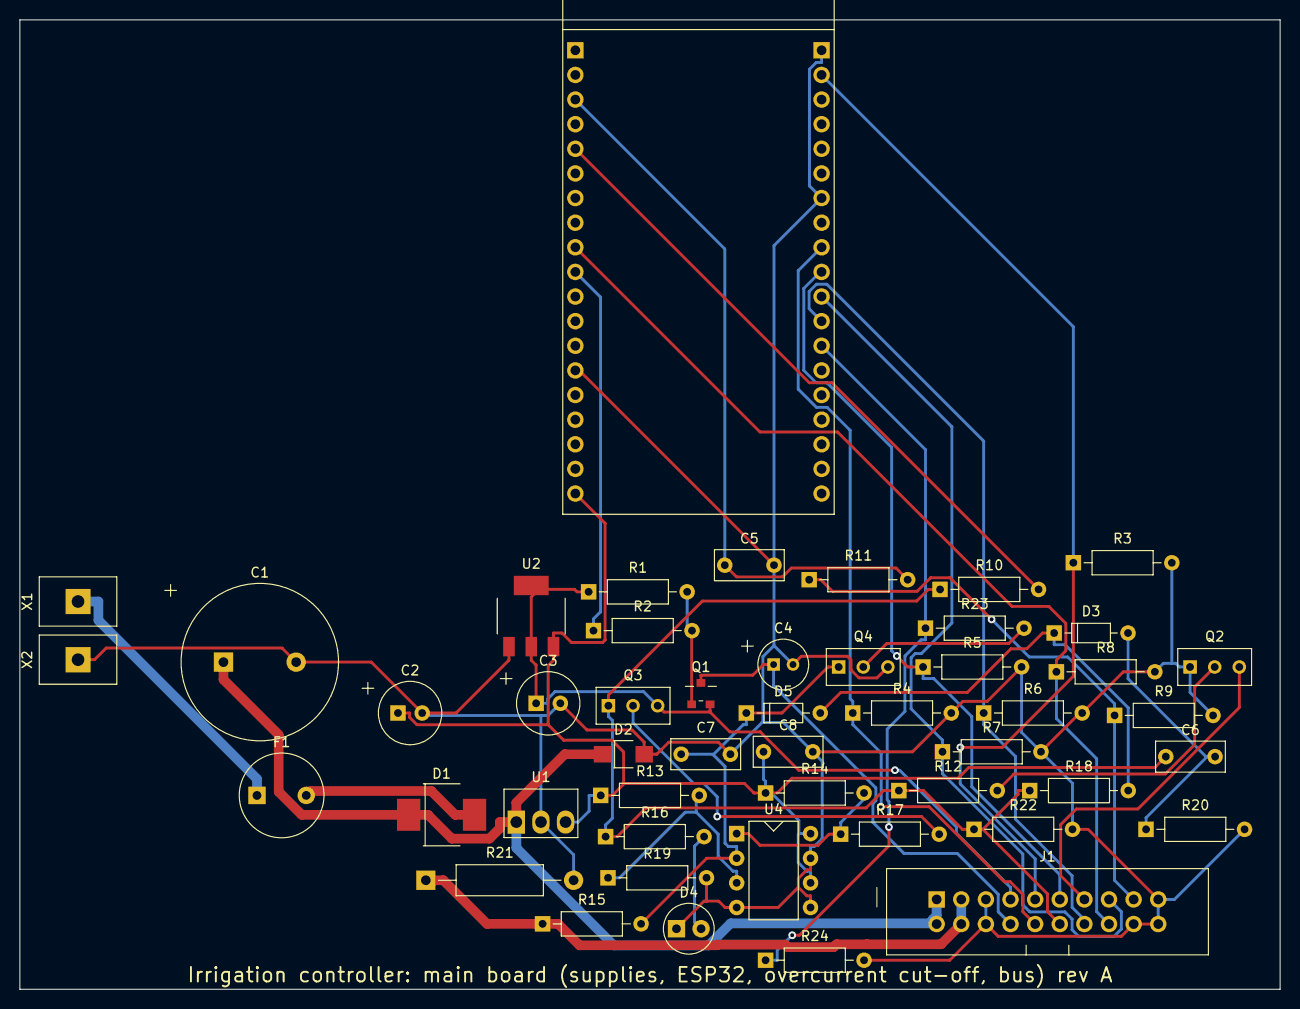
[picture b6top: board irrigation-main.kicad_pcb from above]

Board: 2 copper layers, 130.0 x 100.0 mm, 49 parts (0 on the bottom side), 31 nets.

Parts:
C1: 220u; CP_Radial_D16
C2, C3: 22u; CP_Radial_D6.3
C4: 10u; CP_Radial_D5
C5, C6: 10n; C_Disc_5.08
C7: 1n; C_Disc_5.08
C8: 100n; C_Disc_5.08
D1: SS34; D_SMC
D2: SMAJ33A; D_SMA
D3, D5: 1N4148; D_DO-35
D4: red; LED_D5.0
F1: 3.15; F_TR5
J1: IDC 2x10; IDC_Header_2x10
Q1: AO3401; SOT-23
Q2: 2N2222A; TO-92_Wide
Q3: BC557B; TO-92_Wide
Q4: BC547B; TO-92_Wide
R1, R6, R7, R8, R20, R24: 100k; R_Axial_0207
R2, R10, R11, R15, R16, R19: 1k; R_Axial_0207
R3, R4, R5, R14, R17, R18, R22, R23: 10k; R_Axial_0207
R9: 1M; R_Axial_0207
R12: 4.7k; R_Axial_0207
R13: 22.1k; R_Axial_0207
R21: 0.1; R_Axial_0309
U1: R-78E5.0-1.0; TO-220_Vertical
U2: AMS1117-3.3; SOT-223
U3: ESP32-DevKitC-32E; ESP32_DevKitC
U4: LM393; DIP-8
X1: 24 V DC in +; TerminalBlock_1x1
X2: 24 V DC in -; TerminalBlock_1x1

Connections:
A0: J1.14, R6.1, U3.J3-12
A1: J1.15, R7.1, U3.J3-11
A2: J1.16, R8.1, U3.J1-9
ANA: J1.17, R9.1, R11.1
ANF: C5.1, R11.2, U3.J1-3
BCL: Q4.2, R23.2
BOE: Q3.2, R17.2
BPD: Q2.2, R12.2
CLR: R23.1, R24.1, U3.J3-13
GCL: J1.13, Q2.3
GND: C1.2, C2.2, C3.2, C4.2, C5.2, C7.2, C8.2, D2.2, D4.1, J1.5, J1.6, J1.18, J1.19, J1.20, Q2.1, Q4.3, R3.2, R4.2, R5.2, R6.2, R7.2, R8.2, R9.2, R19.2, R20.2, R21.2, R22.2, R24.2, U1.2, U2.1, U3.J1-14, U3.J3-1, U3.J3-7, U4.4, U4.5, U4.7, X2.1
LFA: D4.2, R16.2
LTA: D3.1, D5.2, R18.2
OCN: R14.2, R17.1, U4.1
OE: J1.12, Q3.1, R10.1, R12.1, R16.1, R18.1, R22.1
OEI: R10.2, U3.J1-5
POR: C6.2, D3.2, R20.1
RCLK: J1.11, R5.1, U3.J3-10
SER: J1.9, R3.1, U3.J3-2
SNSEN: R2.1, U3.J1-10
SRCLK: J1.10, R4.1, U3.J3-9
SRET: J1.3, J1.4, R15.1, R21.1
SRF: C7.1, D5.1, Q4.1, R15.2, U4.2
SSG: Q1.1, R1.2, R2.2
V5: C2.1, C6.1, C8.1, R13.1, R14.1, U1.3, U2.3, U3.J1-19, U4.6, U4.8
V24: C1.1, D1.1, D2.1, J1.1, J1.2, U1.1
V33: C3.1, J1.7, Q1.2, Q3.3, R1.1, U2.2, U2.4
V33S: C4.1, J1.8, Q1.3
VFU: D1.2, F1.2
VIN: F1.1, X1.1
VOC: R13.2, R19.1, U4.3
